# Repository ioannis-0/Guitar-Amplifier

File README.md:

### **Personal Project: Guitar Amplifier**
For this project, Ioannis and Daniel collaborated to design a guitar amplifier. Kicad was used to create a printed circuit board (PCB) compatible with an electric guitar to amplify its output volume.

This project is made up of two phases, with the first one being the **Creation of the PCB**  and the second being the **Testing** phase.

**Creation of the PCB:** Creation of the guitar amplifier PCB was done using KiCad. During this period, issues occured specifically concerning component selection. The components of an operational amplifier, power barrel connector, audio jack, and potentiometer were the main issues that arose. This issue was resolved through thorough research to identify components most compatible with our design goals: 

Operational amplifier = TL072 Lo/Noise 2XJFET Op. Amplifier (https://www.altronics.com.au/p/z2872-tl072-lo-noise-2xjfet-op-amplifier/?srsltid=AfmBOop0Bf4LZ-UD45hlEh1Mb5qex_sKeyiiGoEN5xp1L9ImB8eifREcn_Q)

Power barrel connector = DCJ200-10-A-K1-K (https://www.digikey.com/en/products/detail/gct/DCJ200-10-A-K1-K/9859579?utm_campaign=buynow&utm_medium=aggregator&utm_source=snapeda)

Audio jack = RJ3VM (https://www.mouser.com/ProductDetail/REAN/RJ3VM?utm_campaign=mouser&qs=0rbOLB9uh%252BCOWk8%2FAwcx4Q%3D%3D&utm_medium=online&utm_source=snapedaonline&utm_content=model)

Potentiometer = TC33X-2-103E (https://www.digikey.com/en/products/detail/bourns-inc/TC33X-2-103E/612858?utm_campaign=buynow&utm_medium=aggregator&utm_source=snapeda)

After using these components a DRC (Design Rule Checking) was ran, the results showing no errors.

<ins> This is the KiCad file for the PCB: </ins>          
https://github.com/ioannis-0/Guitar-Amplifier/tree/main/Final%20personal%20project

<ins> Image of the PCB on KiCad: </ins>  

**Testing:** The PCB was tested on an electric guitar (Squier Sonic Stratocaster). The testing we conducted on this electric guitar was a success, as we were able to increase the volume output of the guitar using the PCB we had created. As no serious problems occurred during the testing phase. As the only issue that occurred was during the soldering process we had to modify the audio jack in order for it to work with the PCB, as the modificatiion was just altering the connect point with the PCB and we did that by using lead.

<ins> Images of the physical PCB: </ins>

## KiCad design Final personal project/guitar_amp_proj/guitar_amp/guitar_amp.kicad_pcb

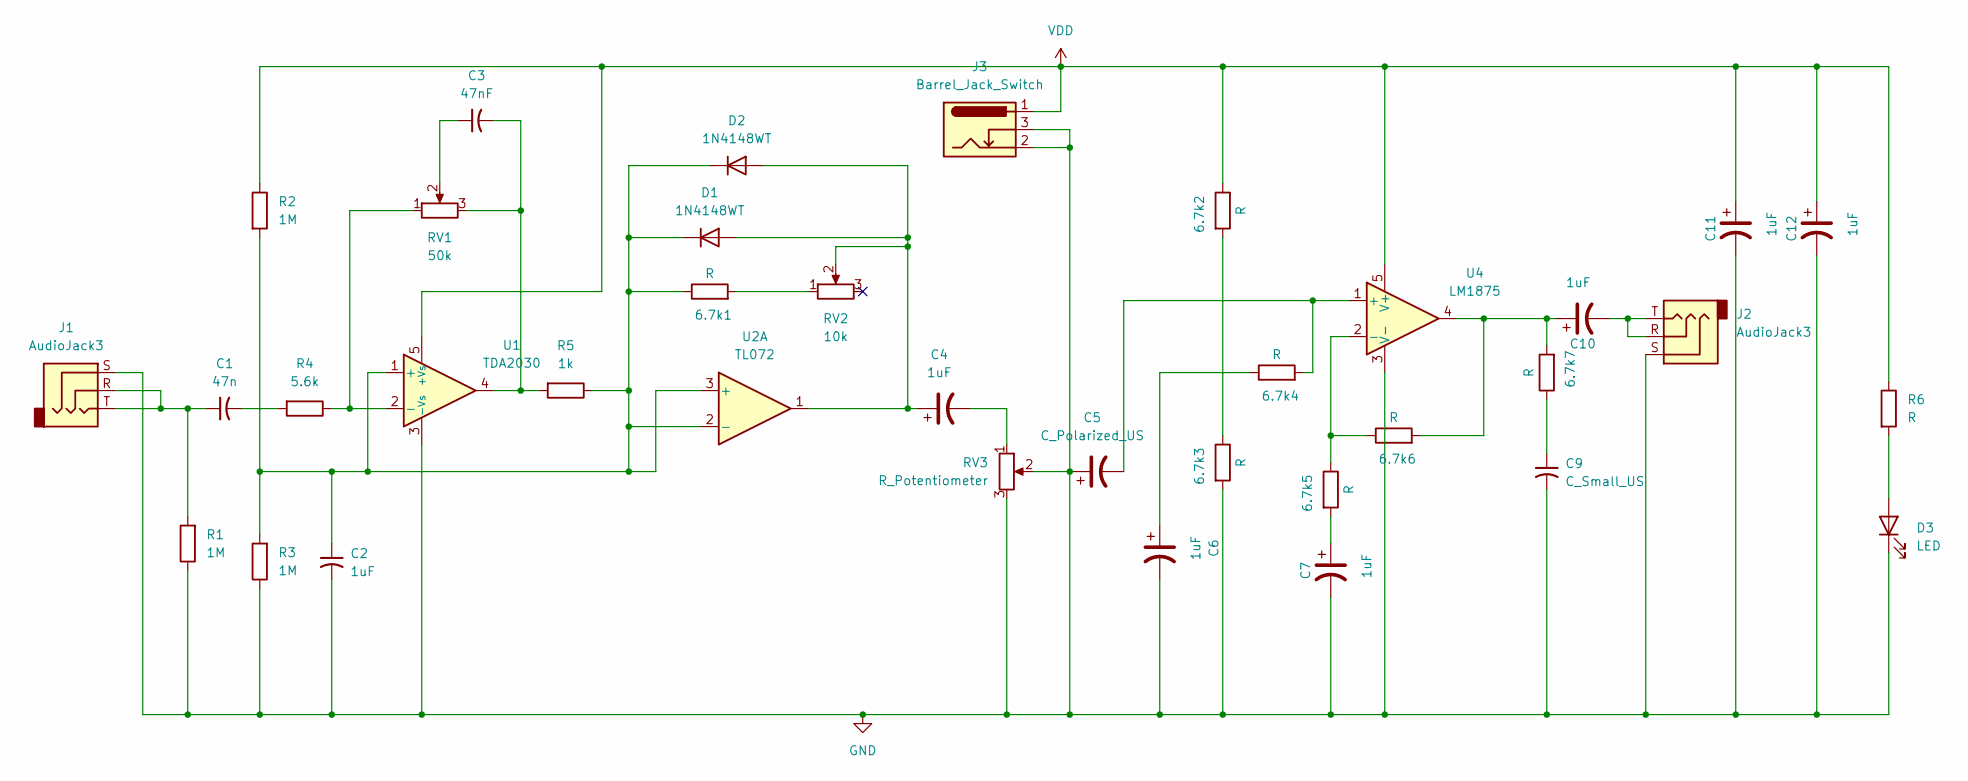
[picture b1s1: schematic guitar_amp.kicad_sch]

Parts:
6.7k1, 6.7k2, 6.7k3, 6.7k4, 6.7k5, 6.7k6, 6.7k7: R; C_0402_1005Metric
C1: 47n; C_0402_1005Metric
C2, C4, C6, C7, C10, C11, C12: 1uF; C_0402_1005Metric
C3: 47nF; C_0402_1005Metric
C5: C_Polarized_US; C_0402_1005Metric
C9: C_Small_US; C_0402_1005Metric
D1, D2: 1N4148WT; D_SOD-523
D3: LED; LEDRD254W57D500H1070
J1, J2: AudioJack3; REAN_RJ3VM
J3: Barrel_Jack_Switch; GCT_DCJ200-10-A-XX-K_REVA
R1, R2, R3: 1M; C_0402_1005Metric
R4: 5.6k; C_0402_1005Metric
R5: 1k; C_0402_1005Metric
R6: R; C_0402_1005Metric
RV1: 50k; TRIM_TC33X-2-103E
RV2: 10k; TRIM_TC33X-2-103E
RV3: R_Potentiometer; TRIM_TC33X-2-103E
U1: TDA2030; TO-220-5_P3.4x3.7mm_StaggerOdd_Lead3.8mm_Vertical
U2: TL072; DIP794W45P254L1060H508Q8
U4: LM1875; TO-220-5_P3.4x3.7mm_StaggerOdd_Lead3.8mm_Vertical

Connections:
GND: 6.7k3.2, C2.2, C5.1, C6.2, C7.2, C9.2, C11.2, C12.2, D3.1 (K), J1.S, J2.S, J3.2, J3.3, R1.1, R3.1, RV3.2, RV3.3, U1.3 (-Vs), U4.3 (V-)
unnamed: 6.7k1.2, RV2.1
unnamed: 6.7k2.2, 6.7k3.1
unnamed: 6.7k4.1, C6.1
unnamed: 6.7k5.2, C7.1
unnamed: 6.7k6.2, 6.7k7.2, C10.1, U4.4
unnamed: 6.7k7.1, C9.1
unnamed: C1.1, J1.R, J1.T, R1.2
unnamed: C1.2, R4.2
unnamed: C3.1, RV1.2
unnamed: C3.2, R5.2, RV1.3, U1.4
unnamed: C4.2, RV3.1
unnamed: C10.2, J2.R, J2.T
unnamed: C4.1, D1.2 (A), D2.2 (A), RV2.2, U2.1
unnamed: 6.7k1.1, C2.1, D1.1 (K), D2.1 (K), R2.2, R3.2, R5.1, U1.1 (+), U2.2 (-), U2.3 (+)
unnamed: D3.2 (A), R6.2
unnamed: R4.1, RV1.1, U1.2 (-)
unnamed: 6.7k4.2, C5.2, U4.1 (+)
unnamed: 6.7k5.1, 6.7k6.1, U4.2 (-)
VDD: 6.7k2.1, C11.1, C12.1, J3.1, R2.1, R6.1, U1.5 (+Vs), U4.5 (V+)

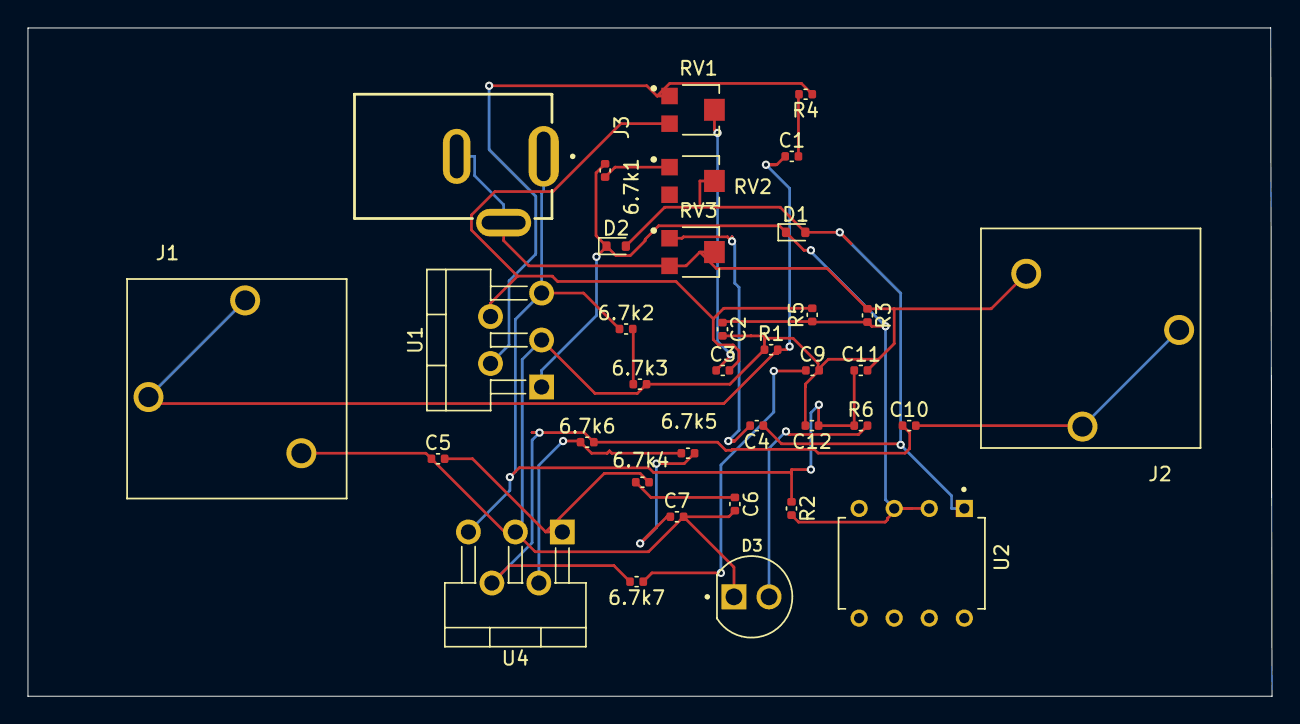
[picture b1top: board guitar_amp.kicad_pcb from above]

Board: 2 copper layers, 90.1 x 48.4 mm, 36 parts (0 on the bottom side), 20 nets.

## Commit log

2025-12-26 this is a test
    testig
2025-12-26 Guitar Amplifier
2025-12-26 Add files via upload
    here u go
2025-12-26 PCB KiCad
2025-12-29 Revise README for clarity and grammar improvements
    Updated the README to clarify the project description and improve grammar.
